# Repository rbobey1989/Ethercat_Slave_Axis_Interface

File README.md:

# Ethercat_Slave_Axis_Interface

Repositorio para el código fuente y aplicaciones del interfaz de esclavo EtherCAT.

Estructura principal:
- `applications/` — aplicaciones PlatformIO y demos
- `firmware/` — código de firmware

Instrucciones:
1. Este repositorio contiene varios proyectos PlatformIO. Usa `platformio run` desde cada aplicación.
2. Añade un remoto (GitHub/GitLab) si quieres copia de seguridad y colaboración.

Contacto: mantén los cambios en ramas y abre PRs para integrarlos.

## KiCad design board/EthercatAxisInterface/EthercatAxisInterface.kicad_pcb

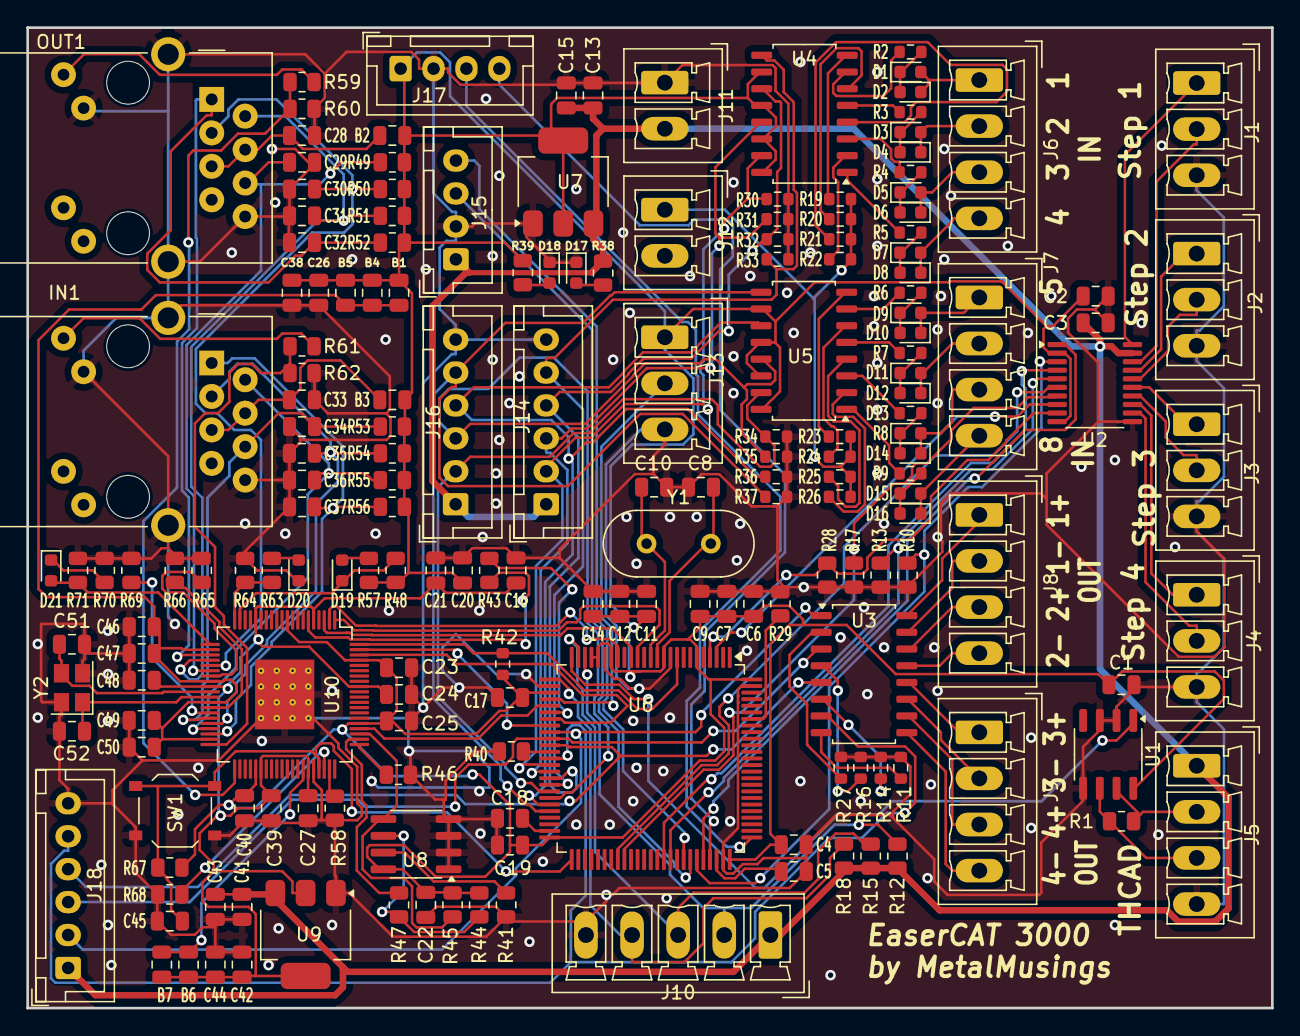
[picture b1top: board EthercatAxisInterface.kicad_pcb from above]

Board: 2 copper layers, 94.5 x 74.4 mm, 184 parts (0 on the bottom side), 140 nets.

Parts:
B1, B4, B5, B6, B7: BLM18EG221SN1D; C_0805_2012Metric
B2, B3: BLM18EG221S; C_0805_2012Metric
C1, C2, C3, C4, C6, C7, C9, C11, C12, C14, C15, C16, C17, C19, C20, C21, C22, C23, C24, C25, C26, C27, C28, C33, C39, C40, C43, C44, C46, C47, C48, C49, C50: 0.1uF; C_0805_2012Metric
C5, C18: 2.2uF; C_0805_2012Metric
C8, C10: 22pF; C_0805_2012Metric
C13, C38, C41, C42: 10uF; C_0805_2012Metric
C29, C30, C31, C32, C34, C35, C36, C37: 10pF; C_0805_2012Metric
C45: 1uF; C_0805_2012Metric
C51, C52: 18pF; C_0805_2012Metric
D1, D3, D5, D7, D9, D11, D13, D15: Yellow led; LED_0603_1608Metric
D2, D4, D6, D8, D10, D12, D14, D16, D20: Red led; LED_0603_1608Metric
D17, D18: Blue led; LED_0603_1608Metric
D19, D21: Green led; LED_0603_1608Metric
IN1: J0011D01BNL; PulseJack JB0011D01BNL
J1: Step1; PhoenixContact_MCV_1,5_3-G-3.5_1x03_P3.50mm_Vertical
J2: Step2; PhoenixContact_MCV_1,5_3-G-3.5_1x03_P3.50mm_Vertical
J3: Step3; PhoenixContact_MCV_1,5_3-G-3.5_1x03_P3.50mm_Vertical
J4: Step4; PhoenixContact_MCV_1,5_3-G-3.5_1x03_P3.50mm_Vertical
J5: THCAD; PhoenixContact_MCV_1,5_4-G-3.5_1x04_P3.50mm_Vertical
J6: In1-4; PhoenixContact_MCV_1,5_4-G-3.5_1x04_P3.50mm_Vertical
J7: In5-8; PhoenixContact_MCV_1,5_4-G-3.5_1x04_P3.50mm_Vertical
J8: Output1-2; PhoenixContact_MCV_1,5_4-G-3.5_1x04_P3.50mm_Vertical
J9: Output3-4; PhoenixContact_MCV_1,5_4-G-3.5_1x04_P3.50mm_Vertical
J10: Encoder; PhoenixContact_MCV_1,5_5-G-3.5_1x05_P3.50mm_Vertical
J11: 5V Power IN; PhoenixContact_MCV_1,5_2-G-3.5_1x02_P3.50mm_Vertical
J12: 24V Field; PhoenixContact_MCV_1,5_2-G-3.5_1x02_P3.50mm_Vertical
J13: DAC; PhoenixContact_MCV_1,5_3-G-3.5_1x03_P3.50mm_Vertical
J14: In_opt1; JST_XH_B6B-XH-A_1x06_P2.50mm_Vertical
J15: Serial usart1; JST_XH_B4B-XH-A_1x04_P2.50mm_Vertical
J16: In_opt2; JST_XH_B6B-XH-A_1x06_P2.50mm_Vertical
J17: STLINK; JST_XH_B4B-XH-A_1x04_P2.50mm_Vertical
J18: Out_opt; JST_XH_B6B-XH-A_1x06_P2.50mm_Vertical
OUT1: J0011D01BNL; PulseJack JB0011D01BNL
R1: 120; R_0805_2012Metric
R2, R3, R4, R5, R6, R7, R8, R9, R42: 4k7; R_0603_1608Metric
R10, R13, R17, R28, R41, R44, R45, R46, R48, R64, R65, R67, R68, R69, R71: 4k7; R_0805_2012Metric
R11, R14, R16, R27: 330; R_0603_1608Metric
R12, R15, R18, R38, R39: 1k; R_0805_2012Metric
R19, R20, R21, R22, R23, R24, R25, R26: 1k; R_0603_1608Metric
R29, R40, R43, R47, R58: 22; R_0805_2012Metric
R30, R31, R32, R33, R34, R35, R36, R37: 39k; R_0603_1608Metric
R49, R50, R51, R52, R53, R54, R55, R56: 49.9; R_0805_2012Metric
R57, R59, R60, R61, R62, R63, R70: 510; R_0805_2012Metric
R66: 12k 1%; R_0805_2012Metric
SW1: SW PB; SW_Push_1P1T_XKB_TS-1187A
U1: MAX3485CSA/ESA; SO-8_3.9x4.9mm_P1.27mm
U2: TXS0108EPW; TSSOP-20_4.4x6.5mm_P0.65mm
U3, U4, U5: TLP292-4; SOIC-16_4.55x10.3mm_P1.27mm
U6: STM32F407VGT6; LQFP-100_14x14mm_P0.5mm
U7: AMS1117-3.3; SOT-223-3_TabPin2
U8: 24LC32A; SOIC-8_3.9x4.9mm_P1.27mm
U9: AMS1117-1.2; SOT-223-3_TabPin2
U10: AX58100; LQFP-80-1EP_10x10mm_P0.4mm_EP5.3x4.5mm_ThermalVias
Y1: 8 MHz; Crystal_HC49-4H_Vertical
Y2: NXK25.000AE12F-KAB6-12; Crystal_SMD_SeikoEpson_TSX3225-4Pin_3.2x2.5mm

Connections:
+1V2: B6.1, B7.1, C16.1, C21.1, C24.1, C27.1, C39.1, C42.1, C44.1, C48.1, U9.2 (VO), U10.5 (VCCK), U10.16 (VCCK), U10.29 (VCCK), U10.46 (VCCK), U10.55 (VCCK), U10.72 (VCCK)
+3.3V: B1.1, B2.1, B3.1, B4.1, B5.1, C1.1, C2.1, C4.1, C6.1, C7.1, C9.1, C11.1, C12.1, C14.1, C17.1, C19.1, C20.1, C22.2, C23.1, C25.1, C26.1, C38.1, C40.1, J13.1, J17.1, R39.2, R42.2, R44.1, R45.1, R48.1, R49.2, R50.2, R51.2, R52.2, R53.2, R54.2, R55.2, R56.2, R57.1, R67.2, U1.8 (VCC), U2.2 (VCCA), U2.10 (OE), U4.10, U4.12, U4.14, U4.16, U5.10, U5.12, U5.14, U5.16, U6.6 (VBAT), U6.11 (VDD), U6.19 (VDD), U6.21 (VREF+), U6.22 (VDDA), U6.28 (VDD), U6.50 (VDD), U6.75 (VDD), U6.100 (VDD), U7.2 (VO), U8.8 (VCC), U10.10 (VCC3IO), U10.45 (VCC3IO), U10.65 (VCC3IO), U10.77 (VCC3IO)
+3.3VA: B1.2, B4.2, B5.2, C46.1, C47.1, C49.1, C50.1, U10.22 (VCC33A), U10.28 (VCC33A), U10.32 (VCC33A), U10.39 (VCC33A)
+5V: C3.1, C13.1, C15.1, C41.1, C43.1, J5.1, J10.1, J11.2, J14.1, J15.1, J16.1, J18.1, R12.2, R15.2, R18.2, R38.2, U2.19 (VCCB), U7.3 (VI), U9.3 (VI)
-24V_FIELD: J12.1, R19.2, R20.2, R21.2, R22.2, R23.2, R24.2, R25.2, R26.2
/STM32F4/BOOT1: R40.2, U6.37 (PB2)
A1V2: B6.2, B7.2, U10.54 (VCC12A_PLL)
DAC1: J13.2, U6.29 (PA4)
EEP_DONE: D21.2 (A), R71.2, U10.21 (EEP_DONE)
ENC_A: J10.2, R12.1, U6.23 (PA0)
ENC_B: J10.3, R15.1, U6.24 (PA1)
ENC_Z: J10.4, R18.1, U6.26 (PA3)
GND: C1.2, C2.2, C3.2, C4.2, C5.1, C6.2, C7.2, C8.1, C9.2, C10.1, C11.2, C12.2, C13.2, C14.2, C15.2, C16.2, C17.2, C18.1, C19.2, C20.2, C21.2, C22.1, C23.2, C24.2, C25.2, C26.2, C27.2, C28.1, C29.1, C30.1, C31.1, C32.1, C33.1, C34.1, C35.1, C36.1, C37.1, C38.2, C39.2, C40.2, C41.2, C42.2, C43.2, C44.2, C45.2, C46.2, C47.2, C48.2, C49.2, C50.2, C51.2, C52.2, D17.1 (K), D18.1 (K), D20.1 (K), IN1.8 (CHS_GND), IN1.10, IN1.SH (CHS_GND), J1.3, J2.3, J3.3, J4.3, J5.4, J10.5, J11.1, J13.3, J14.6, J15.2, J16.6, J17.2, J18.6, OUT1.8 (CHS_GND), OUT1.10, OUT1.SH (CHS_GND), R10.1, R11.2, R13.1, R14.2, R16.2, R17.1, R27.2, R28.1, R29.1, R30.2, R31.2, R32.2, R33.2, R34.2, R35.2, R36.2, R37.2, R40.1, R41.2, R46.1, R58.2, R60.2, R62.2, R64.1, R65.2, R66.2, R68.1, R69.2, R70.1, R71.1, SW1.1, U1.2 (~RE), U1.3 (DE), U1.5 (GND), U2.11 (GND), U6.10 (VSS), U6.20 (VSSA), U6.27 (VSS), U6.74 (VSS), U6.99 (VSS), U7.1 (GND), U8.1 (A0), U8.2 (A1), U8.3 (A2), U8.4 (GND), U9.1 (GND), U10.56 (FM), U10.81 (GND_EPAD), Y2.2, Y2.4
I2C_SCL: R44.2, R47.1, U8.6 (SCL)
I2C_SDA: R45.2, U8.5 (SDA), U10.63 (I2C_SDA)
IO1: J18.2, U3.1, U6.34 (PC5)
IO2: J18.3, U3.3, U6.35 (PB0)
IO3: J18.4, U3.5, U6.36 (PB1)
IO4: J18.5, U3.7, U6.38 (PE7)
IO5: J14.2, R30.1, U4.15, U6.39 (PE8)
IO6: J14.3, R31.1, U4.13, U6.40 (PE9)
IO7: J14.4, R32.1, U4.11, U6.41 (PE10)
IO8: J14.5, R33.1, U4.9, U6.42 (PE11)
IO9: J16.2, R34.1, U5.15, U6.43 (PE12)
IO10: J16.3, R35.1, U5.13, U6.44 (PE13)
IO11: J16.4, R36.1, U5.11, U6.45 (PE14)
IO12: J16.5, R37.1, U5.9, U6.46 (PE15)
LED_ERR: R63.1, R64.2, U10.20 (LED_ERR)
LED_RUN: D19.1 (K), R48.2, U10.19 (LED_RUN)
unnamed: D1.2 (A), D2.1 (K), J6.1
unnamed: D1.1 (K), D2.2 (A), R2.1
unnamed: D3.2 (A), D4.1 (K), J6.2
unnamed: D3.1 (K), D4.2 (A), R3.1
unnamed: D5.2 (A), D6.1 (K), J6.3
unnamed: D5.1 (K), D6.2 (A), R4.1
unnamed: D7.2 (A), D8.1 (K), J6.4
unnamed: D7.1 (K), D8.2 (A), R5.1
unnamed: D9.1 (K), D10.2 (A), R6.1
unnamed: D9.2 (A), D10.1 (K), J7.1
unnamed: D11.2 (A), D12.1 (K), J7.2
unnamed: D11.1 (K), D12.2 (A), R7.1
unnamed: D13.2 (A), D14.1 (K), J7.3
unnamed: D13.1 (K), D14.2 (A), R8.1
unnamed: D15.2 (A), D16.1 (K), J7.4
unnamed: D15.1 (K), D16.2 (A), R9.1
unnamed: D17.2 (A), R38.1
unnamed: D18.2 (A), R39.1
unnamed: D19.2 (A), R57.2
unnamed: D20.2 (A), R63.2
unnamed: D21.1 (K), R70.2
unnamed: IN1.9, R61.2
unnamed: B3.2, C33.2, IN1.4 (TCT), IN1.5 (RCT)
unnamed: J5.2, R1.2, U1.7 (B)
unnamed: J5.3, R1.1, U1.6 (A)
unnamed: J8.1, U3.16
unnamed: J8.2, U3.15
unnamed: J8.3, U3.14
unnamed: J8.4, U3.13
unnamed: J9.1, U3.12
unnamed: J9.2, U3.11
unnamed: J9.3, U3.10
unnamed: J9.4, U3.9
unnamed: OUT1.9, R59.2
unnamed: B2.2, C28.2, OUT1.4 (TCT), OUT1.5 (RCT)
unnamed: R2.2, U4.7
unnamed: R3.2, U4.5
unnamed: R4.2, U4.3
unnamed: R5.2, U4.1
unnamed: R6.2, U5.7
unnamed: R7.2, U5.5
unnamed: R8.2, U5.3
unnamed: R9.2, U5.1
unnamed: R11.1, U3.8
unnamed: R14.1, U3.6
unnamed: R16.1, U3.4
unnamed: R19.1, U4.8
unnamed: R20.1, U4.6
unnamed: R21.1, U4.4
unnamed: R22.1, U4.2
unnamed: R23.1, U5.8
unnamed: R24.1, U5.6
unnamed: R25.1, U5.4
unnamed: R26.1, U5.2
unnamed: R27.1, U3.2
unnamed: R29.2, U6.94 (BOOT0)
unnamed: C8.2, U6.12 (PH0), Y1.2
unnamed: C10.2, U6.13 (PH1), Y1.1
unnamed: C18.2, U6.49 (VCAP_1)
unnamed: C5.2, U6.73 (VCAP_2)
unnamed: R41.1, U8.7 (WP)
unnamed: R47.2, U10.62 (I2C_SCL)
unnamed: R69.1, U10.34 (P0_SD)
unnamed: R65.1, U10.27 (P1_SD)
unnamed: R66.1, U10.33 (RESET_BG)
unnamed: R43.2, U10.6 (SPI_MISO)
unnamed: R58.1, U10.59 (TEST)
P0_ACT: R61.1, R62.1, U10.40 (P0_ACT)
P0_RXIN: C34.2, IN1.6 (RD-), R53.1, U10.35 (P0_RXIN)
P0_RXIP: C35.2, IN1.3 (RD+), R54.1, U10.36 (P0_RXIP)
P0_TXON: C36.2, IN1.2 (TD-), R55.1, U10.37 (P0_TXON)
P0_TXOP: C37.2, IN1.1 (TD+), R56.1, U10.38 (P0_TXOP)
P1_ACT: R59.1, R60.1, U10.41 (P1_ACT)
P1_RXIN: C29.2, OUT1.6 (RD-), R49.1, U10.26 (P1_RXIN)
P1_RXIP: C30.2, OUT1.3 (RD+), R50.1, U10.25 (P1_RXIP)
P1_TXON: C31.2, OUT1.2 (TD-), R51.1, U10.24 (P1_TXON)
P1_TXOP: C32.2, OUT1.1 (TD+), R52.1, U10.23 (P1_TXOP)
PDI_EMU: R46.2, U10.61 (PDI_EMU)
RESET_MCU: C45.1, R67.1, SW1.2, U6.51 (PB12), U10.57 (RSTn)
RSTO: R68.2, U10.58 (RSTO)
RX: J15.3, U6.69 (PA10)
SCS_FUNC: R42.1, U6.9 (PC15), U10.80 (SCS_FUNC)
SINT: U6.15 (PC0), U10.1 (SPI_INT)
SPI_CS: U6.33 (PC4), U10.79 (SCS_ESC)
SPI_MISO: R43.1, U6.31 (PA6)
SPI_MOSI: U6.32 (PA7), U10.78 (SPI_MOSI)
SPI_SCK: U6.30 (PA5), U10.64 (SPI_CLK)
STEP1_DIR: U2.1 (A1), U6.71 (PA12)
STEP1_DIR_OUT: J1.1, U2.20 (B1)
STEP1_STEP: R10.2, U2.3 (A2), U6.70 (PA11)
STEP1_STEP_OUT: J1.2, U2.18 (B2)
STEP2_DIR: U2.4 (A3), U6.65 (PC8)
STEP2_DIR_OUT: J2.1, U2.17 (B3)
STEP2_STEP: R13.2, U2.5 (A4), U6.66 (PC9)
STEP2_STEP_OUT: J2.2, U2.16 (B4)
STEP3_DIR: U2.6 (A5), U6.58 (PD11)
STEP3_DIR_OUT: J3.1, U2.15 (B5)
STEP3_STEP: R17.2, U2.7 (A6), U6.59 (PD12)
STEP3_STEP_OUT: J3.2, U2.14 (B6)
STEP4_DIR: U2.8 (A7), U6.3 (PE4)
STEP4_DIR_OUT: J4.1, U2.13 (B7)
STEP4_STEP: R28.2, U2.9 (A8), U6.4 (PE5)
STEP4_STEP_OUT: J4.2, U2.12 (B8)
SWCLK: J17.3, U6.76 (PA14)
SWDIO: J17.4, U6.72 (PA13)
SYNC0: U6.18 (PC3), U10.2 (SYNC_L0)
SYNC1: U6.16 (PC1), U10.3 (SYNC_L1)
THCAD_CTR: U1.1 (RO), U6.25 (PA2)
TX: J15.4, U6.68 (PA9)
XSCI: C52.1, U10.31 (XSCI), Y2.1
XSCO: C51.1, U10.30 (XSCO), Y2.3

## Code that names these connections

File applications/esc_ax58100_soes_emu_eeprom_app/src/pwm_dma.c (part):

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 *
 * Each axis uses one PWM output from TIM1 and one direction GPIO on GPIOE.
 *
 * Axis 0: PWM PE9  -> TIM1_CH1, DIR PE8
 * Axis 1: PWM PE11 -> TIM1_CH2, DIR PE10
 * Axis 2: PWM PE13 -> TIM1_CH3, DIR PE12
 * Axis 3: PWM PE14 -> TIM1_CH4, DIR PE15
 *
 * DMA is driven from TIM1 update events using DMA2 Stream5 Channel6. The DMA
 * burst updates CCR1..CCR4 together so all PWM channels stay phase-aligned.
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
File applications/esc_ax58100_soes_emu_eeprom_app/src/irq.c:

/* irq.c - minimal ISR implementations and IRQ management for ESC events */
#include "irq.h"
#include "ecat_slv.h"
#include "stm32f4xx_ll_gpio.h"
#include "stm32f4xx_ll_bus.h"
#include "stm32f4xx_ll_exti.h"
#include "stm32f4xx_ll_system.h"

/* Store currently requested ALevent mask so ISR can call worker with it */
volatile uint32_t g_ecat_event_mask = 0;
/* Flag set by minimal SYNC0 ISR to request processing in main context */
volatile uint8_t g_sync0_flag = 0;
/* Flag set by minimal SINT ISR (PC0) to request processing in main context */
volatile uint8_t g_sint_flag = 0;

void esc_hw_int_enable(uint32_t mask)
{
    /* Save mask for ISR and enable the ESC side event mask */
    g_ecat_event_mask = mask;
    ESC_ALeventmaskwrite(ESC_ALeventmaskread() | mask);

    /* Configure GPIOC PC0 as input */
    LL_AHB1_GRP1_EnableClock(LL_AHB1_GRP1_PERIPH_GPIOC);
    LL_GPIO_SetPinMode(GPIOC, LL_GPIO_PIN_0, LL_GPIO_MODE_INPUT);
    LL_GPIO_SetPinPull(GPIOC, LL_GPIO_PIN_0, LL_GPIO_PULL_NO);

    /* Map EXTI line0 to port C */
    LL_APB2_GRP1_EnableClock(LL_APB2_GRP1_PERIPH_SYSCFG);
    LL_SYSCFG_SetEXTISource(LL_SYSCFG_EXTI_PORTC, LL_SYSCFG_EXTI_LINE0);

    /* Configure EXTI0 trigger both edges (robust for unknown polarity) */
    LL_EXTI_EnableRisingTrig_0_31(LL_EXTI_LINE_0);
    LL_EXTI_EnableFallingTrig_0_31(LL_EXTI_LINE_0);

    /* Enable EXTI0 interrupt and NVIC */
    LL_EXTI_EnableIT_0_31(LL_EXTI_LINE_0);
    NVIC_SetPriority(EXTI0_IRQn, 3);
    NVIC_EnableIRQ(EXTI0_IRQn);

    /* If DC SYNC0 requested, configure PC3 EXTI for SYNC0 (minimal ISR) */
    if (mask & ESCREG_ALEVENT_DC_SYNC0)
    {
        /* Configure PC3 as input */
        LL_GPIO_SetPinMode(GPIOC, LL_GPIO_PIN_3, LL_GPIO_MODE_INPUT);
        LL_GPIO_SetPinPull(GPIOC, LL_GPIO_PIN_3, LL_GPIO_PULL_NO);

        /* Map EXTI line3 to port C */
        LL_SYSCFG_SetEXTISource(LL_SYSCFG_EXTI_PORTC, LL_SYSCFG_EXTI_LINE3);

        /* Configure EXTI3 trigger on rising edge (SYNC often rising) */
        LL_EXTI_EnableRisingTrig_0_31(LL_EXTI_LINE_3);
        LL_EXTI_DisableFallingTrig_0_31(LL_EXTI_LINE_3);

        /* Enable EXTI3 interrupt and NVIC */
        LL_EXTI_EnableIT_0_31(LL_EXTI_LINE_3);
        NVIC_SetPriority(EXTI3_IRQn, 3);
        NVIC_EnableIRQ(EXTI3_IRQn);
    }
}

void esc_hw_int_disable(uint32_t mask)
{
    /* Clear requested mask bits in ESC ALEVENTMASK */
    uint32_t cur = ESC_ALeventmaskread();
    cur &= ~mask;
    ESC_ALeventmaskwrite(cur);

    /* Disable EXTI0 and NVIC (leave SYSCFG/GPIO config as-is) */
    LL_EXTI_DisableIT_0_31(LL_EXTI_LINE_0);
    NVIC_DisableIRQ(EXTI0_IRQn);
    g_ecat_event_mask = 0;

    /* If disabling DC SYNC0, disable EXTI3 as well */
    if (mask & ESCREG_ALEVENT_DC_SYNC0)
    {
        LL_EXTI_DisableIT_0_31(LL_EXTI_LINE_3);
        NVIC_DisableIRQ(EXTI3_IRQn);
        g_sync0_flag = 0;
    }
}

/* EXTI0 IRQ handler: clear flag, disable line briefly to avoid re-entry,
 * signal main loop for processing */
void EXTI0_IRQHandler(void)
{
    if (LL_EXTI_IsActiveFlag_0_31(LL_EXTI_LINE_0))
    {
        LL_EXTI_ClearFlag_0_31(LL_EXTI_LINE_0);
        LL_EXTI_DisableIT_0_31(LL_EXTI_LINE_0);
        g_sint_flag = 1;
    }
}

/* Minimal SYNC0 handler (PC3). Latch and delegate processing to main context. */
void EXTI3_IRQHandler(void)
{
    if (LL_EXTI_IsActiveFlag_0_31(LL_EXTI_LINE_3))
    {
        LL_EXTI_ClearFlag_0_31(LL_EXTI_LINE_3);
        LL_EXTI_DisableIT_0_31(LL_EXTI_LINE_3);
        g_sync0_flag = 1;
    }
}

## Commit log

2026-05-06 Initial commit: add .gitignore and README
2026-05-06 Crear repositorio con dos apps una destinada a funcionamiento con eeprom fisica y otra con eeprom emulada
2026-05-06 Añadido readme PIN_USAGE.md con el recuento de pines por app, se ha implementado para probar la emulacion de eeprom en su app correspondiente
2026-05-07 añadido captura de canal z, expuesto por PDO Status Level y Latch
2026-05-07 actualización de remapeo de pines GPIOs
2026-05-12 añadido modulo vel_ctrl
2026-05-13 se cambia el estimador de velocidad y se cambia la arquitectura de la placa a 2 ejes
